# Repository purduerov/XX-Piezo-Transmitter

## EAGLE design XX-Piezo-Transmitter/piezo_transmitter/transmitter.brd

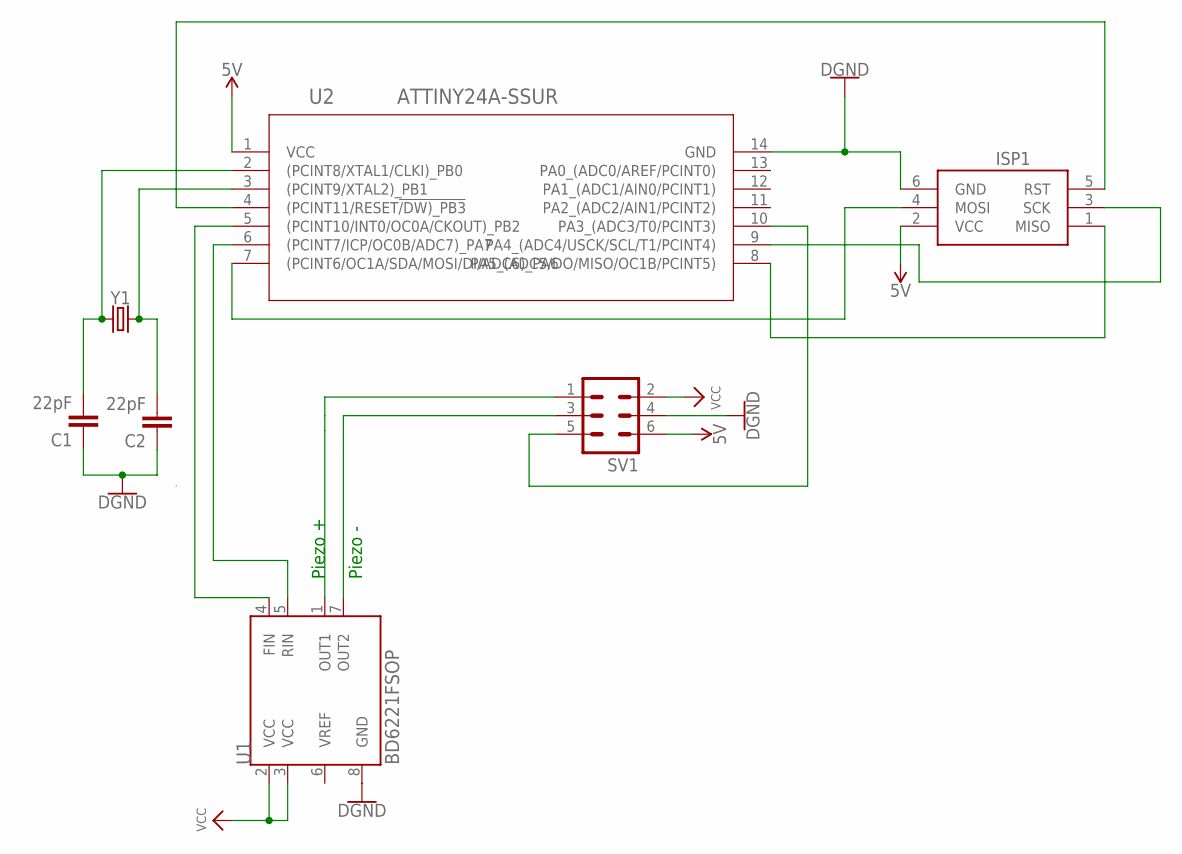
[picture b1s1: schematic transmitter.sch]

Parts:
C1, C2: 22pF; 0603
ISP1: AVRISP-6; AVRISP
SV1: MA03-2
U1: BD6221FSOP; SOP8
U2: ATTINY24A-SSUR; 14S1
Y1: CRYSTALPTH-HC49US; HC49US

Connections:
5V: ISP1.2 (VCC), SV1.6, U2.1 (VCC)
12V: SV1.2, U1.2 (VCC), U1.3 (VCC)
FIN: U1.4 (FIN), U2.5 ((PCINT10/INT0/OC0A/CKOUT)_PB2)
GND: C1.1, C2.1, ISP1.6 (GND), SV1.4, U1.8 (GND), U2.14 (GND)
IO: SV1.5, U2.10 (PA3_(ADC3/T0/PCINT3))
MISO: ISP1.1 (MISO), U2.8 (PA5_(ADC5/DO/MISO/OC1B/PCINT5))
MOSI: ISP1.4 (MOSI), U2.7 ((PCINT6/OC1A/SDA/MOSI/DI/ADC6)_PA6)
PIEZO+: SV1.1, U1.1 (OUT1)
PIEZO-: SV1.3, U1.7 (OUT2)
RESET: ISP1.5 (RST), U2.4 ((PCINT11/RESET!/DW)_PB3)
RIN: U1.5 (RIN), U2.6 ((PCINT7/ICP/OC0B/ADC7)_PA7)
SCK: ISP1.3 (SCK), U2.9 (PA4_(ADC4/USCK/SCL/T1/PCINT4))
XTAL1: C1.2, U2.2 ((PCINT8/XTAL1/CLKI)_PB0), Y1.1
XTAL2: C2.2, U2.3 ((PCINT9/XTAL2)_PB1), Y1.2

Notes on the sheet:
Piezo +
Piezo -

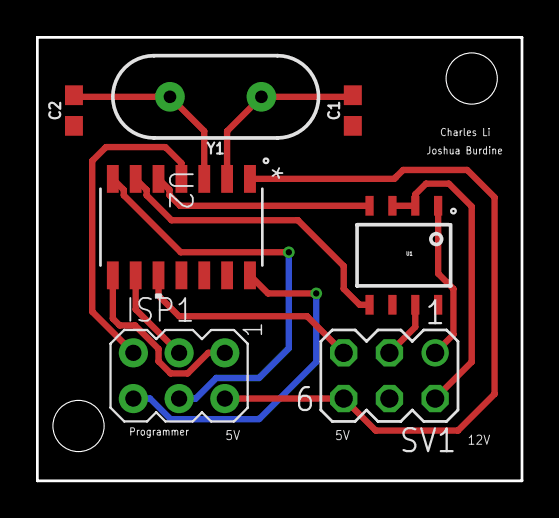
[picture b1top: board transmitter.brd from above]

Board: 2 copper layers, 26.9 x 24.6 mm, 7 parts (0 on the bottom side), 14 nets.

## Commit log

2018-01-23 Adding Files
2018-02-02 Added pin headers & pwm line, crystal and caps change.
2018-02-02 Removed bad directory
2018-02-12 Change to through hole crystal. Change to LV 22pf cap.
2018-02-15 Fixed oscillator trace lengths and board trace widths. Added programmer header and mounting holes. Board about 1 squ in now.
2018-02-15 Removed temp files, added gitignore so they stay gone, and fixed a trace width from 6->14 mil
2018-02-17 Made oscillator to capacitor length approximately equal
2018-02-18 Fixed trace names

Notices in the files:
parts and their libraries:
SparkFun-Retired: Licensing: Creative Commons ShareAlike 4.0 International - https://creativecommons.org/licenses/by-sa/4.0
